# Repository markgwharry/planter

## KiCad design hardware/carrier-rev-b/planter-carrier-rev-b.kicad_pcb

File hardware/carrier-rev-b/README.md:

# Planter XIAO carrier - Rev B (PCB, C6 or S3)

Rev A's circuit turned into a 2-layer PCB that sits directly behind the WeAct
1.54-inch e-paper module. It takes a **socketed** Seeed XIAO ESP32-C6 **or**
ESP32-S3; the firmware build picks the chip, the board doesn't care.

Status (2026-10-27): on-board 1S protection added (DW01A + FS8205A), the
antenna keep-out removed (external antenna), LCSC numbers on every
machine-placeable part, and all silkscreen at or above JLCPCB's legend
minimums (1.0 mm text, 0.15 mm lines). ERC clean, DRC clean with **zero** violations
including warnings, schematic parity clean, 0 unconnected; the exported
netlist was checked pin by pin against `netlist.csv` and the two datasheets.
Nothing has been fabricated, fitted or powered. First-article gates below.

| Top | Underside (display side) |
|---|---|
|  |  |

## What changed from Rev A

| Item | Rev A (perfboard P1) | Rev B | Why |
|---|---|---|---|
| XIAO mounting | Soldered | **2x7 2.54mm sockets/pins** | Swap C6/S3. Gives access to the underside BAT pads. Room for 0603s underneath. |
| Pin map | By C6 GPIO | **By XIAO pad label** | The castellations are common to C6 and S3. Arduino's `D0..D10` resolve per chip. |
| EPD BUSY | D6 | **D7** | D6 is UART0 TX on both chips. The ROM log drives it on every wake into the BUSY pin of an unpowered panel. D7 (RX) is an input from reset. |
| Battery to XIAO | Wires | **J4 wire pads** beside U1 | The underside BAT pads differ between C6 and S3, so no pads are copied into the footprint. |
| Test points | 10 | **3** (PACK+, GND, 3V3_SW) | Every other net is on a XIAO castellation, which you can probe while it's socketed. |
| Connectors | TBD | **JST-PH side-entry** S2B (battery) / S3B (probe) | Cables exit the bottom edge, next to the USB-C. |
| Display | Cabled 2x4 | **2x4 female socket on the underside** | The module's own header plugs straight in. |
| Cell protection | External PCB on the cell | **On board: DW01A (U2) + FS8205A (Q2)** | J1 takes a bare or a protected cell. |
| Antenna | Over a copper keep-out | **No keep-out**; ground pour under the module | An external antenna is used (see Antenna). |

Electrical values are otherwise unchanged: 200k/200k divider + 100 nF, AO3401A
high-side switch with 100k pull-up and 1k gate resistor, 1k + 100 nF on the
probe input, 10 uF + 2 x 100 nF on 3V3_SW.

## Battery protection

Standard DW01A low-side circuit, values from the PUOLOP DW01A datasheet:

| Part | Value | Connection |
|---|---|---|
| U2 DW01A (C351410) | SOT-23-6 | GND to the cell negative (PACK_IN-), TD open |
| Q2 FS8205A (C2830320) | SOT-23-6, 1 S1, 2 D, 3 S2, 4 G2, 5 D, 6 G1 | FET1 (S1/G1) = discharge, S1 to PACK_IN-; FET2 (S2/G2) = charge, S2 to GND |
| R6 | 100R | PACK+ to U2 VCC. Fed after JP1 so U2's ~3 uA shows in the sleep measurement |
| C6 | 100 nF | U2 VCC to PACK_IN- |
| R7 | 1k | U2 VM/CS to GND |

Trips at 4.30 V over-charge, 2.50 V over-discharge, and 150 mV across Q2
(roughly 3 A). GND is the protected pack negative; PACK_IN- must never be
joined to it. The XIAO's own charger (C6 ~100 mA, S3 ~50 mA) charges through
Q2, so the over-charge cut-off backs it up. U2/Q2 sit along the bottom edge
under the XIAO's USB end (they are 1.1 mm tall; the module is on 8.5 mm
sockets). R6/C6/R7 sit between J1 and J4.

## Pin map (both chips)

| XIAO pad | Net | C6 GPIO | S3 GPIO |
|---|---|---:|---:|
| D0/A0 | VBAT_ADC | 0 | 1 |
| D1/A1 | MOIST_ADC | 1 | 2 |
| D2 | PERIPH_EN_N (LOW = on) | 2 | 3 |
| D3 | EPD_CS | 21 | 4 |
| D4 | EPD_DC | 22 | 5 |
| D5 | EPD_RST | 23 | 6 |
| D6 | spare (UART TX) | 16 | 43 |
| D7 | EPD_BUSY | 17 | 44 |
| D8 | EPD_SCLK | 19 | 7 |
| D9 | spare (S3 default MISO) | 20 | 8 |
| D10 | EPD_MOSI | 18 | 9 |

S3 D2 = GPIO3 is a JTAG-source strapping pin. It is only sampled if the eFuse
selects it, and R1 holds it high anyway.

## Mechanical stack

```
   XIAO (USB-C at bottom edge, antenna end up)  ── on 2x7 female sockets
   ─────────── Rev B carrier, 50.12 x 32.60 mm, 1.6 mm ───────────
      J3 2x4 female socket (underside) + 4 x M2.5 standoffs, ~11 mm
   ─────────── WeAct 1.54" module (header pins pointing back) ───────────
   ─────────── e-paper panel ───────────
```

- The outline, the M2.5 hole pattern (44.52 x 27.00 mm) and the right-edge FPC
  recess all copy the WeAct board-shape drawing, so the carrier sits exactly
  over the module.
- J3 pin 1 is at (1.93, 12.49) mm from the top-left corner in the top view,
  measured off the drawing. **Check it against a real module before ordering.**
- Standoff length = socket height + header plastic. 8.5 mm socket + 2.5 mm
  plastic ≈ 11 mm. Measure your parts.
- A low-profile XIAO (male pins soldered direct) still clears the 0603s
  underneath it. You lose the ability to swap chips.

## Antenna

Both chips run from an **external U.FL antenna**, so the board has no antenna
keep-out and the ground pour runs under the whole module. Leave room in the
enclosure for the cable and whip.

The XIAO ESP32-C6 defaults to its built-in ceramic antenna, which now sits over
ground. Firmware must select the U.FL: drive GPIO3 LOW (enables the RF switch),
wait ~100 ms, then drive GPIO14 HIGH (external antenna). The plain XIAO
ESP32-S3 only has the U.FL.

## Battery

The cell goes to J1 (pin 1 = cell +, pin 2 = cell -); a bare or a protected
cell is fine. **JST-PH LiPo polarity is not standardised: check every pigtail
before plugging in.** JP1 is the removable current-measurement link. PACK+ then
goes to J4.1 and, by a short strain-relieved wire, to the XIAO's underside
BAT+. J4.2 (protected GND) goes to BAT-. On the C6 the BAT- pad is the one
near the D8 marking and BAT+ the one near D5.

Hand-fitted parts that are not in the JLCPCB BOM: the XIAO and its two 1x7
2.54 mm female sockets, J3 (2x4 2.54 mm female socket, underside), J4 and JP1
(1x2 2.54 mm headers) plus a jumper shunt for JP1, and four M2.5 standoffs
(~11 mm).

## Files

| File | Purpose |
|---|---|
| `netlist.csv` | Reviewed connectivity. `make_kicad.py` builds the schematic from it. |
| `make_kicad.py` | Writes `planter-carrier-rev-b.kicad_sch` and `Planter.kicad_sym`. |
| `make_pcb.py` | Writes the custom XIAO footprint and `planter-carrier-rev-b.kicad_pcb`. It takes nets from the schematic's exported netlist, so parity holds by construction. Needs KiCad's bundled Python. |
| `check.sh` | Regenerates everything. Fails on any ERC, DRC or parity finding. |
| `make_fab.sh` | Into `build/fab/`: Gerber/drill zip; `-bom.csv` and `-cpl-top.csv` for JLCPCB assembly (only parts with an LCSC number, every designator listed in full); `-bom-full.csv` with everything, including the hand-fitted parts. JLCPCB centres each part on its CPL coordinate, so through-hole parts (J1, J2) are written at the centre of their pins, not KiCad's pin-1 anchor. Check JLCPCB's placement preview: SOT-23 and SOT-23-6 rotations sometimes need correcting there. |

Both generators are reproducible baselines. If you edit in the KiCad GUI,
commit before re-running them.

## Firmware

`platformio-rev-b.ini` at the repo root:

```
pio run -c platformio-rev-b.ini -e esp32c6_rev_b -t upload
pio run -c platformio-rev-b.ini -e esp32s3_rev_b -t upload
```

Both set `PLANTER_CARRIER_REV_B`, which selects the D-label pin map in
`firmware-v2/planter_v2.cpp`. The S3 moisture endpoints are placeholders
(the C6 P1 figures) until it is calibrated.

## First-article gates

Carried over from Rev A, plus Rev B items:

1. Before ordering: print the top silk 1:1 and lay it over a real WeAct module.
   Check the holes, the J3 pin 1 position and the FPC recess.
2. Check every battery pigtail's polarity against J1 (pin 1 = cell +).
   Before the first cell: power J1 from a current-limited bench supply in
   place of the cell. Check that GND follows the supply negative at 3.7 V,
   that the output cuts off as the supply drops below ~2.5 V, and that it
   comes back once the supply is raised above ~2.9 V.
3. With USB removed: A0 reads half of PACK+ within resistor tolerance.
   Firmware battery voltage agrees with a DMM within 50 mV after `BATT_TRIM`.
4. 3V3_SW is fully off between wakes. No EPD line is high while it is off.
   Check BUSY (now D7) in particular.
5. Measure whole-assembly sleep current at JP1, separately for C6 and S3.
   Use a low-burden meter (e.g. a PPK2): U2 is powered after JP1, so a
   high-burden uA range can drop its supply enough to trip it under load.
   Don't ground-reference the cell or J1.2 while USB is on an earthed PC:
   that bypasses Q2.
6. Recalibrate dry/wet endpoints on each chip.
7. Check Wi-Fi RSSI at the install site with the enclosure closed, C6 first,
   with the external antenna selected (GPIO3 LOW, GPIO14 HIGH).
8. 24-hour soak with repeated Wi-Fi and display updates, on each chip.

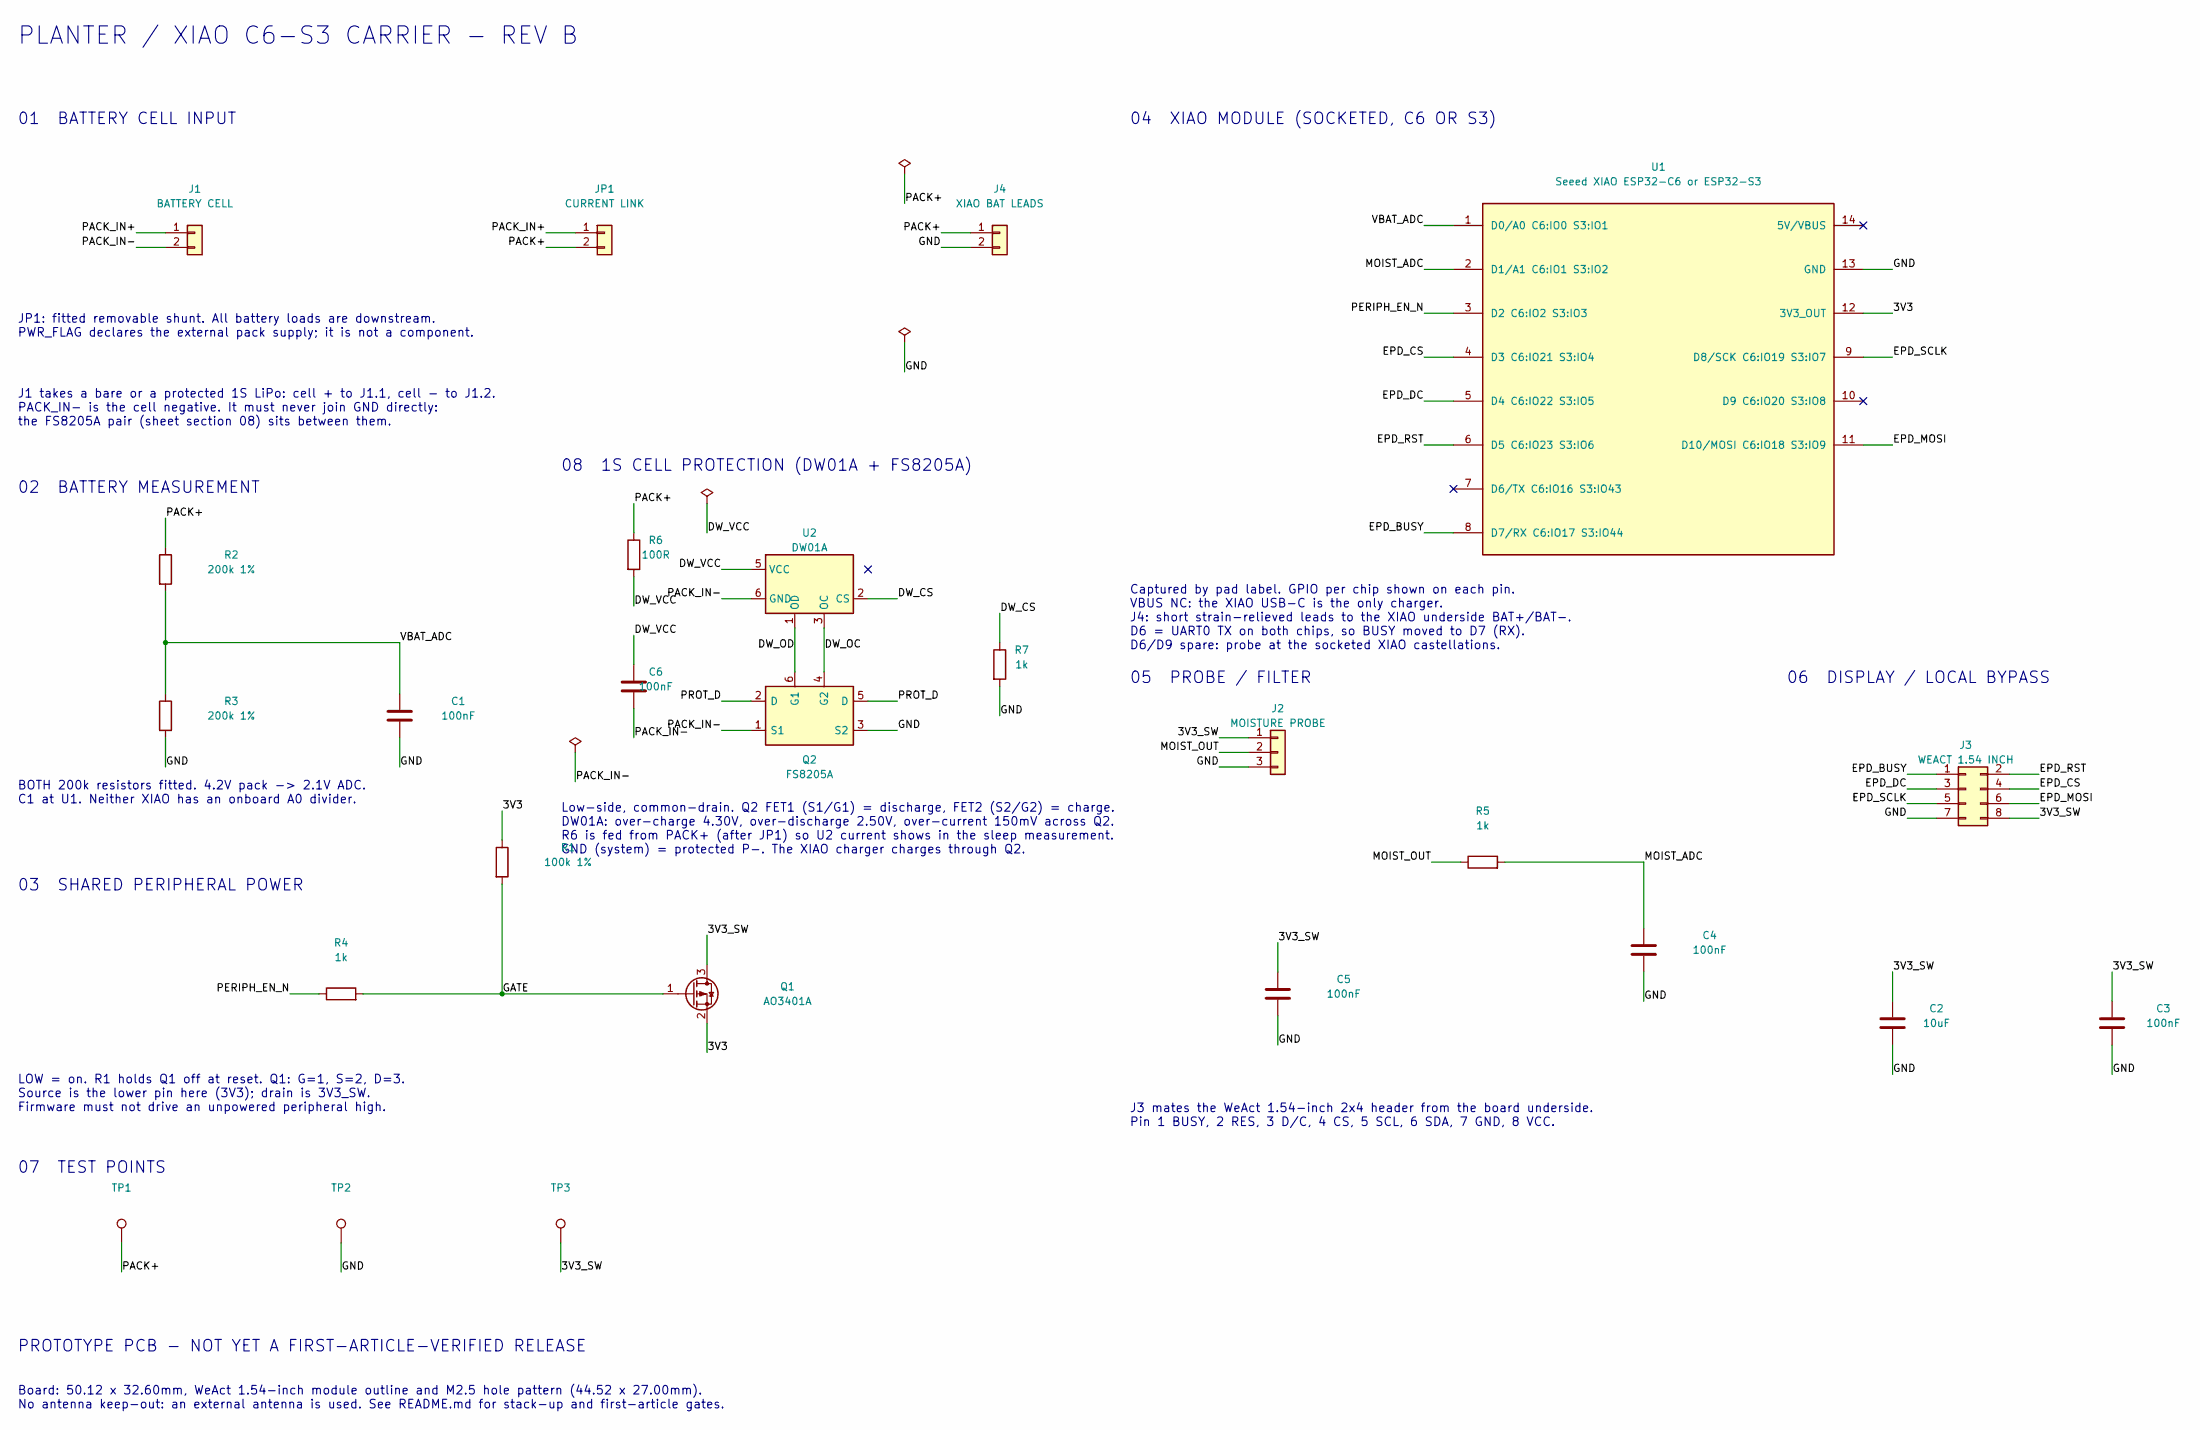
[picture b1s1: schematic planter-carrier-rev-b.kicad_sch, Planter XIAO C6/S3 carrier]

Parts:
C1, C3, C4, C5, C6: 100nF; C_0603_1608Metric; LCSC C14663
C2: 10uF; C_0805_2012Metric; LCSC C15850
J1: BATTERY CELL; JST_PH_S2B-PH-K_1x02_P2.00mm_Horizontal; LCSC C173752
J2: MOISTURE PROBE; JST_PH_S3B-PH-K_1x03_P2.00mm_Horizontal; LCSC C157929
J3: WEACT 1.54 INCH; PinSocket_2x04_P2.54mm_Vertical
J4: XIAO BAT LEADS; PinHeader_1x02_P2.54mm_Vertical
JP1: CURRENT LINK; PinHeader_1x02_P2.54mm_Vertical
Q1: AO3401A; SOT-23; LCSC C15127
Q2: FS8205A; SOT-23-6; LCSC C2830320
R1: 100k 1%; R_0603_1608Metric; LCSC C25803
R2, R3: 200k 1%; R_0603_1608Metric; LCSC C25811
R4, R5, R7: 1k; R_0603_1608Metric; LCSC C21190
R6: 100R; R_0603_1608Metric; LCSC C22775
TP1: TP1; TestPoint_Pad_D1.5mm
TP2: TP2; TestPoint_Pad_D1.5mm
TP3: TP3; TestPoint_Pad_D1.5mm
U1: Seeed XIAO ESP32-C6 or ESP32-S3; Seeed_XIAO_Socketed_2x7_P2.54mm
U2: DW01A; SOT-23-6; LCSC C351410

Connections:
/3V3: Q1.2 (S), R1.1, U1.12 (3V3_OUT)
/3V3_SW: C2.1, C3.1, C5.1, J2.1, J3.8, Q1.3 (D), TP3.1
/DW_CS: R7.1, U2.2 (CS)
/DW_OC: Q2.4 (G2), U2.3 (OC)
/DW_OD: Q2.6 (G1), U2.1 (OD)
/DW_VCC: C6.1, R6.2, U2.5 (VCC)
/EPD_BUSY: J3.1, U1.8 (D7/RX C6:IO17 S3:IO44)
/EPD_CS: J3.4, U1.4 (D3 C6:IO21 S3:IO4)
/EPD_DC: J3.3, U1.5 (D4 C6:IO22 S3:IO5)
/EPD_MOSI: J3.6, U1.11 (D10/MOSI C6:IO18 S3:IO9)
/EPD_RST: J3.2, U1.6 (D5 C6:IO23 S3:IO6)
/EPD_SCLK: J3.5, U1.9 (D8/SCK C6:IO19 S3:IO7)
/GATE: Q1.1 (G), R1.2, R4.2
/GND: C1.2, C2.2, C3.2, C4.2, C5.2, J2.3, J3.7, J4.2, Q2.3 (S2), R3.2, R7.2, TP2.1, U1.13 (GND)
/MOIST_ADC: C4.1, R5.2, U1.2 (D1/A1 C6:IO1 S3:IO2)
/MOIST_OUT: J2.2, R5.1
/PACK+: J4.1, JP1.2, R2.1, R6.1, TP1.1
/PACK_IN+: J1.1, JP1.1
/PACK_IN-: C6.2, J1.2, Q2.1 (S1), U2.6 (GND)
/PERIPH_EN_N: R4.1, U1.3 (D2 C6:IO2 S3:IO3)
/PROT_D: Q2.2 (D), Q2.5 (D)
/VBAT_ADC: C1.1, R2.2, R3.1, U1.1 (D0/A0 C6:IO0 S3:IO1)

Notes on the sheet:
PLANTER / XIAO C6-S3 CARRIER - REV B
01 BATTERY CELL INPUT
JP1: fitted removable shunt. All battery loads are downstream. PWR_FLAG declares the external pack supply; it is not a component.
J1 takes a bare or a protected 1S LiPo: cell + to J1.1, cell - to J1.2. PACK_IN- is the cell negative. It must never join GND directly: the FS8205A pair (sheet section 08) sits between them.
08 1S CELL PROTECTION (DW01A + FS8205A)
Low-side, common-drain. Q2 FET1 (S1/G1) = discharge, FET2 (S2/G2) = charge. DW01A: over-charge 4.30V, over-discharge 2.50V, over-current 150mV across Q2. R6 is fed from PACK+ (after JP1) so U2 current shows in the sleep measurement. GND (system) = protected P-. The XIAO charger charges through Q2.
02 BATTERY MEASUREMENT
BOTH 200k resistors fitted. 4.2V pack -> 2.1V ADC. C1 at U1. Neither XIAO has an onboard A0 divider.
03 SHARED PERIPHERAL POWER
LOW = on. R1 holds Q1 off at reset. Q1: G=1, S=2, D=3. Source is the lower pin here (3V3); drain is 3V3_SW. Firmware must not drive an unpowered peripheral high.
04 XIAO MODULE (SOCKETED, C6 OR S3)
Captured by pad label. GPIO per chip shown on each pin. VBUS NC: the XIAO USB-C is the only charger. J4: short strain-relieved leads to the XIAO underside BAT+/BAT-. D6 = UART0 TX on both chips, so BUSY moved to D7 (RX). D6/D9 spare: probe at the socketed XIAO castellations.
05 PROBE / FILTER
06 DISPLAY / LOCAL BYPASS
J3 mates the WeAct 1.54-inch 2x4 header from the board underside. Pin 1 BUSY, 2 RES, 3 D/C, 4 CS, 5 SCL, 6 SDA, 7 GND, 8 VCC.
07 TEST POINTS
PROTOTYPE PCB - NOT YET A FIRST-ARTICLE-VERIFIED RELEASE
Board: 50.12 x 32.60mm, WeAct 1.54-inch module outline and M2.5 hole pattern (44.52 x 27.00mm). No antenna keep-out: an external antenna is used. See README.md for stack-up and first-article gates.

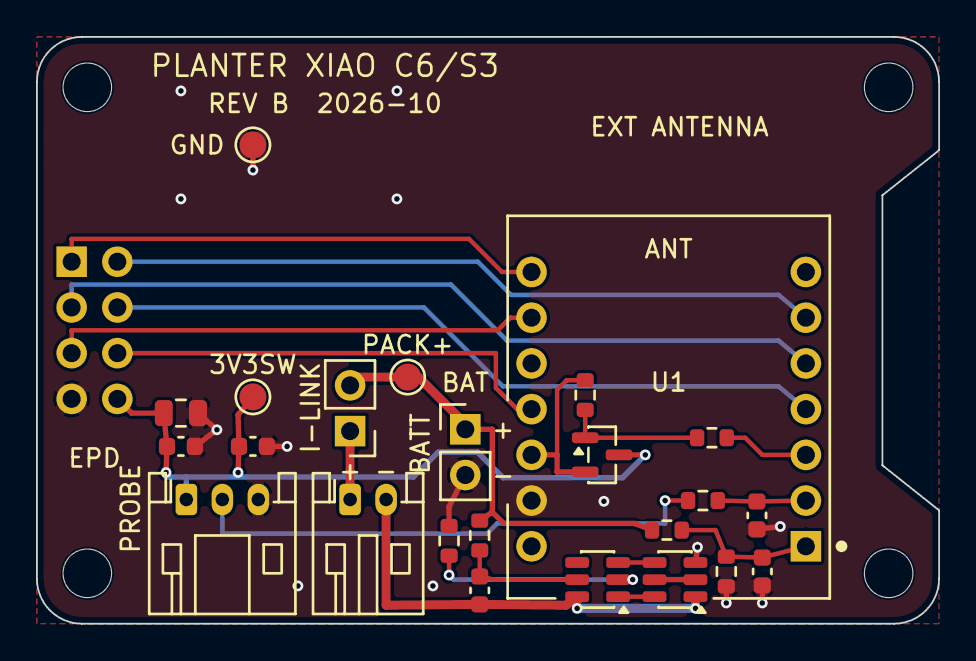
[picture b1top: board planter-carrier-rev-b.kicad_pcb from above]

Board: 2 copper layers, 50.1 x 32.6 mm, 29 parts (1 on the bottom side), 22 nets.

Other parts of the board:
H1, H2, H3, H4: M2.5; MountingHole_2.7mm_M2.5

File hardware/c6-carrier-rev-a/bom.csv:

Reference,Quantity,Value or part,Package,Fit,Notes
U1,1,Seeed XIAO ESP32-C6,XIAO SMT module,Fitted,Use official footprint and antenna keepout
Q1,1,AO3401A,SOT-23,Fitted,P-channel high-side switch
R1,1,100k 1%,0603,Fitted,Q1 gate pull-up to 3V3
R2,1,200k 1%,0603,Fitted,Protected PACK+ to VBAT_ADC
R3,1,200k 1%,0603,Fitted,Mandatory VBAT_ADC to GND; no onboard divider resistor
R4,1,1k 1%,0603,Fitted,D2 to Q1 gate
R5,1,1k 1%,0603,Fitted,Moisture analogue series resistor
C1,1,100nF 10V X7R,0603,Fitted,VBAT_ADC filter at U1
C2,1,10uF 10V X5R,0805,Fitted,3V3_SW bulk decoupling at J3
C3,1,100nF 10V X7R,0603,Fitted,3V3_SW high-frequency decoupling at J3
C4,1,100nF 10V X7R,0603,Fitted,MOIST_ADC filter at U1
C5,1,100nF 10V X7R,0603,Fitted,3V3_SW decoupling at J2
J1,1,Keyed battery connector 2-way,TBD,Fitted,Pin 1 P+; pin 2 P-; match protected pack
J2,1,Keyed moisture connector 3-way,TBD,Fitted,Pin 1 3V3_SW; 2 AOUT; 3 GND
J3,1,2x4 shrouded header 2.54mm,TH 2x4,Fitted,Pinout matches supplied WeAct module
JP1,1,2-pin removable current link,2.54mm TH,Fitted,Normally shorted; series with P+
TP1-TP10,10,Test point,1.5mm SMD,Fitted,See README layout requirements

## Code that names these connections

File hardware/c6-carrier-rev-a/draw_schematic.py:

"""Render the reviewed circuit drawing; matching net labels are connected.

This is an SVG review artifact, not a KiCad schematic or ERC substitute.
Run from any directory: python3 draw_schematic.py
"""
from pathlib import Path
from html import escape

parts = ['<svg xmlns="http://www.w3.org/2000/svg" width="1600" height="1160" viewBox="0 0 1600 1160">',
         '<style>text{font-family:Arial,sans-serif;fill:#172b3a} .wire{stroke:#216351;stroke-width:2;fill:none}</style>',
         '<rect width="1600" height="1160" fill="#f4f7f6"/>']


def text(x, y, s, size=16, bold=False):
    parts.append(f'<text x="{x}" y="{y}" font-size="{size}" font-weight="{700 if bold else 400}">{escape(s)}</text>')


def line(x1, y1, x2, y2):
    parts.append(f'<path class="wire" d="M{x1},{y1} L{x2},{y2}"/>')


def box(x, y, w, h, title):
    parts.append(f'<rect x="{x}" y="{y}" width="{w}" height="{h}" rx="10" fill="white" stroke="#bacbc4"/>')
    text(x+20, y+32, title, 20, True)


def resistor(x, y, ref, value, left, right):
    text(x, y-9, left, 14)
    line(x, y, x+150, y)
    parts.append(f'<rect x="{x+150}" y="{y-8}" width="56" height="16" fill="white" stroke="#216351" stroke-width="2"/>')
    line(x+206, y, x+360, y)
    text(x+148, y-16, f'{ref} {value}', 14, True)
    text(x+222, y-9, right, 14)
    text(x+137, y+22, '1', 12)
    text(x+211, y+22, '2', 12)


def capacitor(x, y, ref, value, net):
    text(x, y-9, net, 14)
    line(x, y, x+167, y)
    line(x+167, y-11, x+167, y+11)
    line(x+180, y-11, x+180, y+11)
    line(x+180, y, x+360, y)
    text(x+149, y-18, f'{ref} {value}', 14, True)
    text(x+265, y-9, 'GND', 14)


text(30, 42, 'PLANTER / XIAO ESP32-C6 / REV A', 29, True)
text(30, 72, 'Electrical review: 2026-09-05. Matching net names connect across sections. All resistors/capacitors shown are FITTED.', 17)
box(30, 100, 495, 465, '1  Protected battery and complete divider')
text(50, 165, 'J1.1 P+ -- JP1.1 [removable link] JP1.2 -- PACK+', 16)
text(50, 196, 'J1.2 P- -------------------------------- GND', 16)
text(50, 228, 'PACK+ -> XIAO BAT+; GND -> XIAO BAT- and GND', 15)
resistor(65, 291, 'R2', '200k 1%', 'PACK+', 'VBAT_ADC')
resistor(65, 352, 'R3', '200k 1%', 'VBAT_ADC', 'GND')
capacitor(65, 416, 'C1', '100nF', 'VBAT_ADC')
text(50, 463, 'A0 = PACK+ / 2; at 4.2V pack, A0 = 2.1V.', 16, True)
text(50, 493, 'R3 is mandatory. XIAO R10 belongs to its charger.', 16)
text(50, 523, 'All battery loads, including R2, are after JP1.', 16)
text(50, 546, 'External common-port protection; no raw B- to GND.', 15)

box(545, 100, 510, 465, '2  Shared peripheral power / active LOW')
text(565, 165, 'Q1 AO3401A / SOT-23', 18, True)
text(565, 197, 'Pad 2 (S) = 3V3; pad 3 (D) = 3V3_SW', 17)
text(565, 228, 'Pad 1 (G) = GATE; body diode D -> S', 17)
resistor(580, 291, 'R1', '100k', '3V3', 'GATE')
resistor(580, 352, 'R4', '1k', 'PERIPH_EN_N', 'GATE')
capacitor(580, 416, 'C2', '10uF', '3V3_SW')
capacitor(580, 481, 'C3', '100nF', '3V3_SW')
text(565, 525, 'C2/C3 at J3. R1 holds Q1 off during reset.', 16)
text(565, 548, 'Park EPD outputs LOW before removing power.', 16)

box(1075, 100, 495, 465, '3  XIAO interface / U1')
xiao = [('1 D0 / GPIO0', 'VBAT_ADC'), ('2 D1 / GPIO1', 'MOIST_ADC'),
        ('3 D2 / GPIO2', 'PERIPH_EN_N'), ('4 D3 / GPIO21', 'EPD_CS'),
        ('5 D4 / GPIO22', 'EPD_DC'), ('6 D5 / GPIO23', 'EPD_RST'),
        ('7 D6 / GPIO16', 'EPD_BUSY'), ('8 D7 / GPIO17', 'SPARE_D7'),
        ('9 D8 / GPIO19', 'EPD_SCLK'), ('10 D9 / GPIO20', 'SPARE_D9'),
        ('11 D10 / GPIO18', 'EPD_MOSI'), ('12 3V3_OUT', '3V3'),
        ('13 GND', 'GND'), ('14 VBUS', 'NO CONNECT')]
for i, (pin, net) in enumerate(xiao):
    text(1095, 164+i*27, pin, 16)
    text(1330, 164+i*27, net, 16, True)

box(30, 585, 495, 415, '4  Moisture interface / J2')
text(50, 650, '1 = 3V3_SW     2 = MOIST_OUT     3 = GND', 17, True)
resistor(65, 719, 'R5', '1k', 'MOIST_OUT', 'MOIST_ADC')
capacitor(65, 790, 'C4', '100nF', 'MOIST_ADC')
capacitor(65, 861, 'C5', '100nF', '3V3_SW')
text(50, 910, 'C4 at U1; C5 at J2. Probe power is 3.3V.', 16)
text(50, 942, 'J2 connector/cable pin order must be confirmed.', 16)
text(50, 973, 'Cable ESD component selection remains open.', 16)

box(545, 585, 510, 415, '5  WeAct module / J3 2x4 / 2.54mm')
epd = [('1 BUSY', 'EPD_BUSY'), ('2 RES', 'EPD_RST'), ('3 D/C', 'EPD_DC'),
       ('4 CS', 'EPD_CS'), ('5 SCL', 'EPD_SCLK'), ('6 SDA', 'EPD_MOSI'),
       ('7 GND', 'GND'), ('8 VCC', '3V3_SW')]
for i, (pin, net) in enumerate(epd):
    text(570, 650+i*31, pin, 17)
    text(780, 650+i*31, net, 17, True)
text(570, 925, 'Header rows: [1 2] [3 4] [5 6] [7 8]', 16)
text(570, 953, 'MISO unused; BUSY uses an MCU pull-down.', 16)
text(570, 980, 'Verify actual panel controller before flashing.', 16)

box(1075, 585, 495, 415, '6  Carrier test points')
for i, net in enumerate(['PACK+', 'GND', '3V3', '3V3_SW', 'VBAT_ADC',
                          'MOIST_ADC', 'PERIPH_EN_N', 'EPD_BUSY', 'SPARE_D7', 'SPARE_D9']):
    text(1095, 650+i*33, f'TP{i+1}', 16)
    text(1210, 650+i*33, net, 16, True)

text(30, 1040, 'ASSEMBLY: underside BAT contacts and connector footprints need mechanical confirmation. USB charging cover deferred.', 17, True)
text(30, 1075, 'REVIEW STATUS: corrected circuit specification. Native KiCad capture/ERC, board layout/DRC and bench validation remain outstanding.', 17)
text(30, 1110, 'Sources: Seeed XIAO C6 schematic 2026-01-14 (03 Power); AOS AO3401A datasheet; supplied WeAct 1.54-inch board drawing.', 16)
text(30, 1138, 'Supporting files: netlist.csv, bom.csv, README.md, review.md. This SVG is not a fabrication release.', 16)
parts.append('</svg>')
Path(__file__).with_name('carrier-schematic.svg').write_text('\n'.join(parts)+'\n')

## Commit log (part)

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2026-05-04 Update firmware, telegraf config, and grafana dashboard
